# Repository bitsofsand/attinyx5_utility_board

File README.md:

Simple utility board for ATTinyx5 microcontrollers. 

More info at http://www.nirya.be/bitsofsand/attinyx5-utility-board/

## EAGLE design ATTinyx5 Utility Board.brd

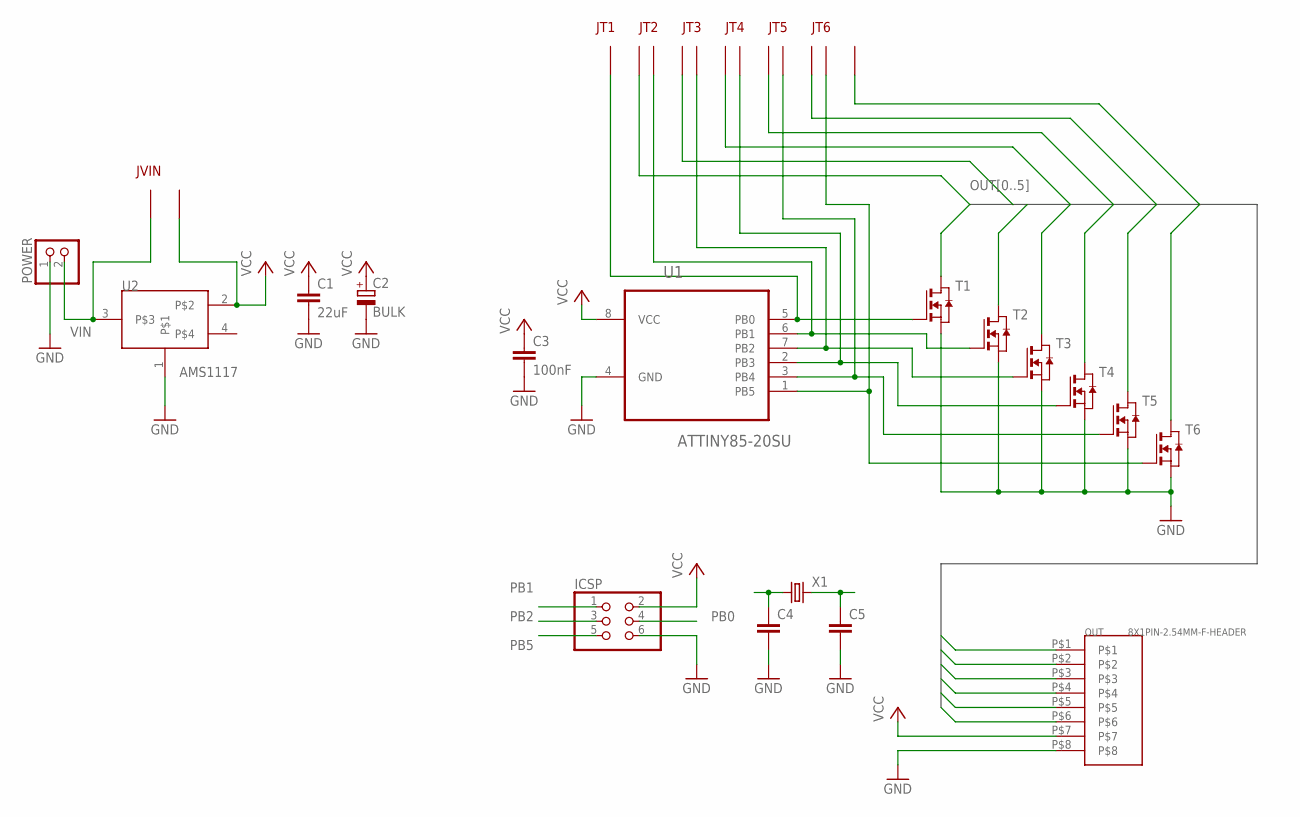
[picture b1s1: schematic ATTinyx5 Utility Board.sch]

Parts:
C1: 22uF; C1206
C2: BULK; E3,5-10
C3: 100nF; C0805
C4, C5: C-EUC0805; C0805
ICSP: PINHD-2X3; 2X03
JT1, JT2, JT3, JT4, JT5, JT6: SOLDER_JUMPER; 1206
JVIN: SOLDER_JUMPER; 1206
OUT: 8X1PIN-2.54MM-F-HEADER; 8X1-2.54MM
POWER: PINHD-1X2; 1X02
T1, T2, T3, T4, T5, T6: NMOSSOT23; SOT-23
U1: ATTINY85-20SU; SOIC127P798X216-8N
U2: AMS1117; SOT223
X1: CRYSTALSM49; SM49

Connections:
GND: C1.2, C2.-, C3.2, C4.2, C5.2, ICSP.6, OUT.P$8, POWER.1, T1.2 (S), T2.2 (S), T3.2 (S), T4.2 (S), T5.2 (S), T6.2 (S), U1.4 (GND), U2.1
OUT0: JT1.P$2, OUT.P$1, T1.1 (D)
OUT1: JT2.P$2, OUT.P$2, T2.1 (D)
OUT2: JT3.P$2, OUT.P$3, T3.1 (D)
OUT3: JT4.P$2, OUT.P$4, T4.1 (D)
OUT4: JT5.P$2, OUT.P$5, T5.1 (D)
OUT5: JT6.P$2, OUT.P$6, T6.1 (D)
PB0: ICSP.4, JT1.P$1, T1.3 (G), U1.5 (PB0)
PB1: ICSP.1, JT2.P$1, T2.3 (G), U1.6 (PB1)
PB2: ICSP.3, JT3.P$1, T3.3 (G), U1.7 (PB2)
PB3: C4.1, JT4.P$1, T4.3 (G), U1.2 (PB3), X1.1
PB4: C5.1, JT5.P$1, T5.3 (G), U1.3 (PB4), X1.2
PB5: ICSP.5, JT6.P$1, T6.3 (G), U1.1 (PB5)
VCC: C1.1, C2.+, C3.1, ICSP.2, JVIN.P$2, OUT.P$7, U1.8 (VCC), U2.2
VIN: JVIN.P$1, POWER.2, U2.3

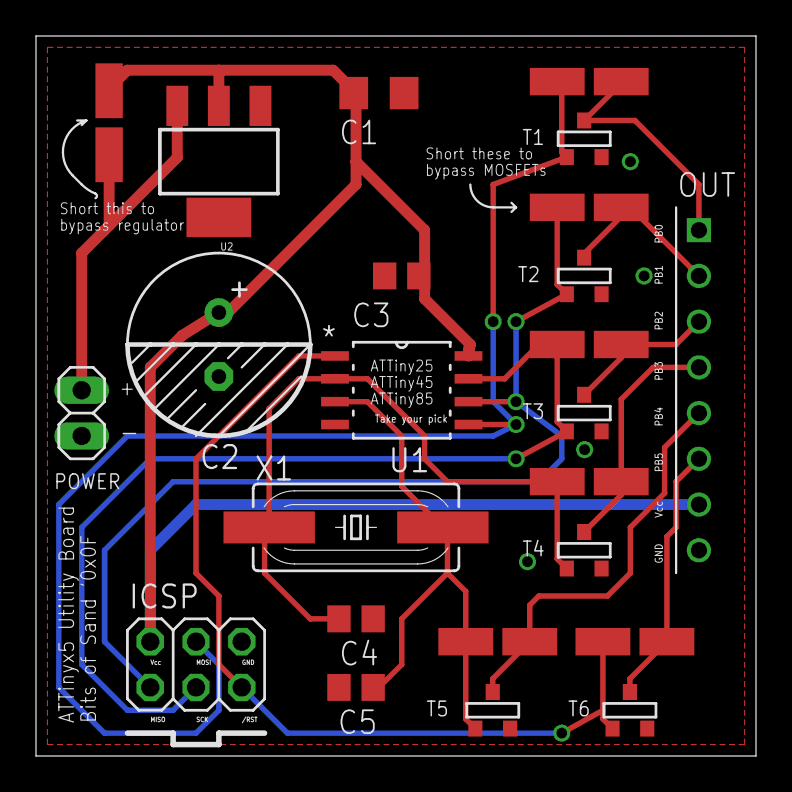
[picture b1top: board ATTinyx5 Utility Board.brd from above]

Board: 2 copper layers, 40.0 x 40.0 mm, 24 parts (0 on the bottom side), 15 nets.

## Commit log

2016-03-05 Initial git import
